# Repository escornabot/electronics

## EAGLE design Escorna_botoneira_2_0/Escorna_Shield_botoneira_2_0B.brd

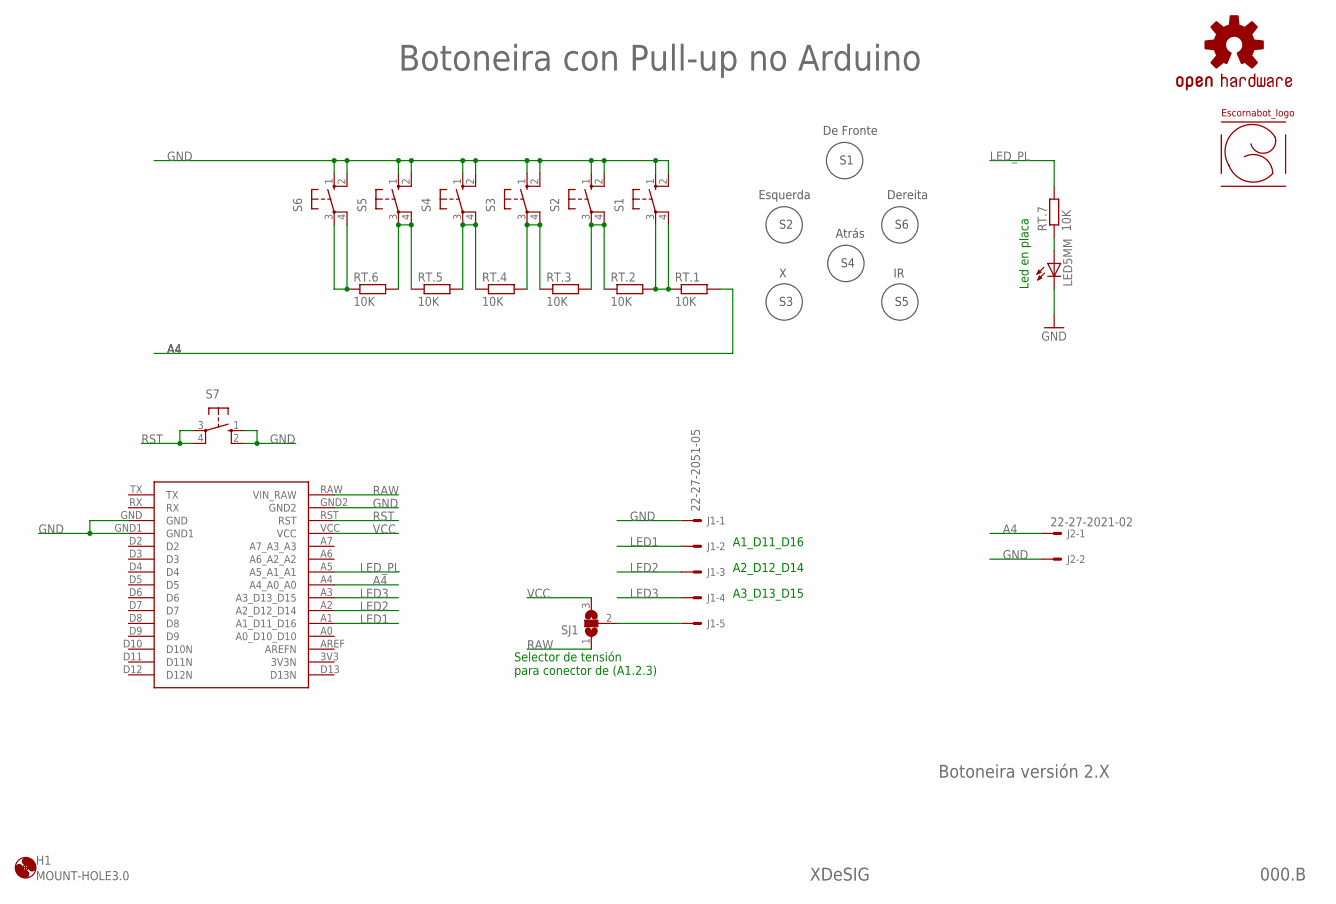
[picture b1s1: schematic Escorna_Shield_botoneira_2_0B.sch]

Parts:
ESSH1: OUTL_ESCORNASHILED; OUTL_ESCORNASHIELD
H1: MOUNT-HOLE3.0; 3,0
J1: 22-27-2051-05; 6410-05
J2: 22-27-2021-02; 6410-02
LED5MM: LED5MM
LOGO2: OSHW-LOGOS; OSHW-LOGO-S
RT.1, RT.2, RT.3, RT.4, RT.5, RT.6, RT.7: 10K; 0204/7
S1, S2, S3, S4, S5, S6: B3F-40XX; B3F40XX_NH
S7: 10-XX; B3F-10XX
SJ1: SOLDERJUMPER_2WAY; SJ_2
U$1: ESCORNABOT; ESCORNA_PEQUE

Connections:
A4: ESSH1.A4 (A4_A0_A0), J2.1, RT.1.2
GND: ESSH1.GND, ESSH1.GND1, ESSH1.GND2, J1.1, J2.2, LED5MM.K (C), S1.1 (S), S1.2 (S1), S2.1 (S), S2.2 (S1), S3.1 (S), S3.2 (S1), S4.1 (S), S4.2 (S1), S5.1 (S), S5.2 (S1), S6.1 (S), S6.2 (S1), S7.1 (S), S7.2 (S1); also elsewhere on the board
LED1: ESSH1.A1 (A1_D11_D16), J1.2
LED2: ESSH1.A2 (A2_D12_D14), J1.3
LED3: ESSH1.A3 (A3_D13_D15), J1.4
LED_PL: ESSH1.A5 (A5_A1_A1), RT.7.2
unnamed 6: LED5MM.A, RT.7.1; also elsewhere on the board
unnamed: J1.5, SJ1.2
unnamed: RT.6.1, S6.3, S6.4 (P1)
unnamed: RT.1.1, RT.2.2, S1.3, S1.4 (P1)
unnamed: RT.2.1, RT.3.2, S2.3, S2.4 (P1)
unnamed: RT.3.1, RT.4.2, S3.3, S3.4 (P1)
unnamed: RT.4.1, RT.5.2, S4.3, S4.4 (P1)
unnamed: RT.5.1, RT.6.2, S5.3, S5.4 (P1)
RAW: ESSH1.RAW (VIN_RAW), SJ1.1
RST: ESSH1.RST, S7.3, S7.4 (P1)
VCC: ESSH1.VCC, SJ1.3

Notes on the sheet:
Botoneira con Pull-up no Arduino
000.B
Botoneira versión 2.X
XDeSIG
De Fronte
Esquerda
Dereita
Atrás
Led en placa
A1_D11_D16
A2_D12_D14
A3_D13_D15
Selector de tensión para conector de (A1.2.3)

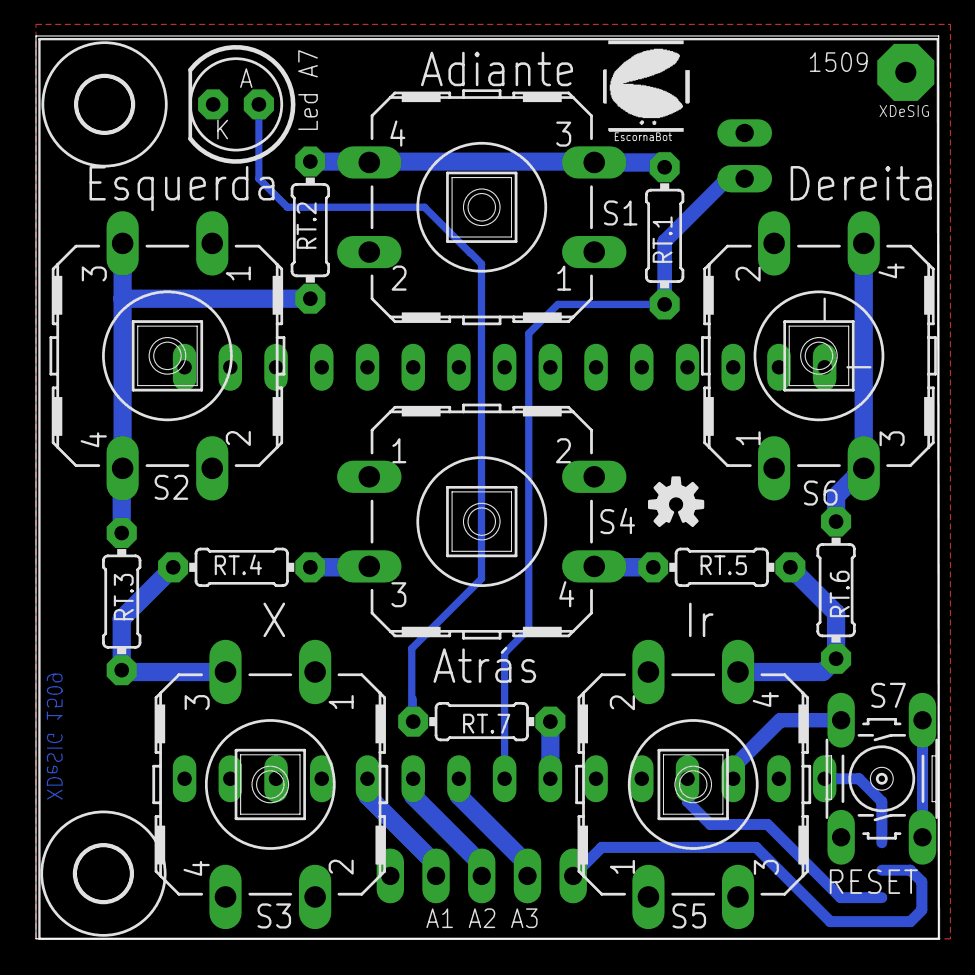
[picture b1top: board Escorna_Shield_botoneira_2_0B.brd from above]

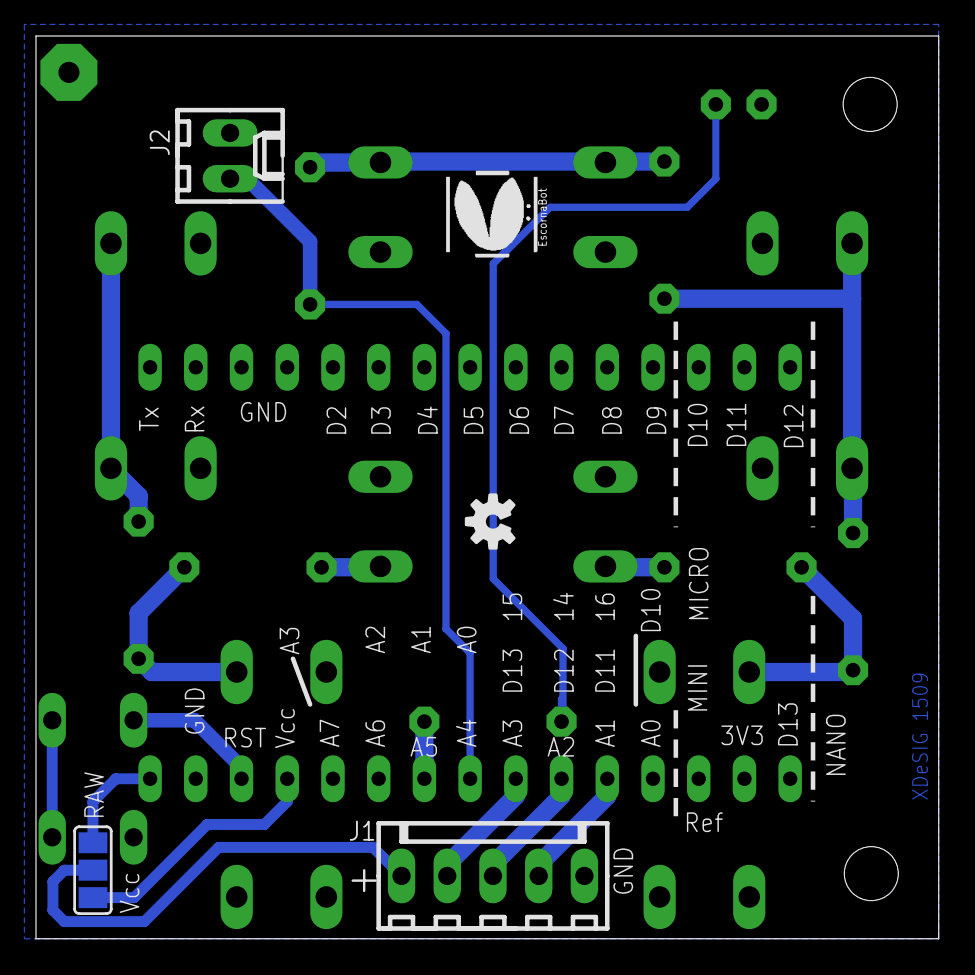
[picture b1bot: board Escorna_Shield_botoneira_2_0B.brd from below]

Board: 2 copper layers, 50.2 x 50.2 mm, 24 parts (5 on the bottom side), 17 nets.

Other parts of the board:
D1: 3 a 5mm; LED5MM
LOGO1: OSHW-LOGOS; OSHW-LOGO-S
U$2: ESCORNABOT; ESCORNA_PEQUE

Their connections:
GND: D1.K; also elsewhere on the board
unnamed 6: D1.A; also elsewhere on the board

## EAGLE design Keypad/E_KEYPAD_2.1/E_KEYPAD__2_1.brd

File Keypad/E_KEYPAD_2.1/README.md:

# Escornabot electronics

## Catalog

- [Escorna CPU][CPU01] (by [Xdesig][XDE01]) is a board to use with
  Arduino Nano. () It integrates keypad on board.
- [Arduino Shield][ARD01] (by [Xdesig][XDE01]) is an Arduino Uno compatible
  shield ready to use with the Escornabot's motors and also integrates a keypad.
- [Cervus][CER01] (by [Xdesig][XDE01]) is a board based on powerful ATmega32u4
  microcontroler and compatible with Arduino shields.
- [Keypad][KEY01] (by [Xdesig][XDE01]) is a 50x50mm board with 5 or 6 buttons and
  connects to any Escornabot.

## License

Every content in this repo, otherwise specified under subdirectories, is
licensed under [Creative Commons BY-SA](LICENSE).

## To buy boards

Developers don't produce boards to sell. Under [_providers_](providers)
directory there are instructions to order yourself.

Are you a board provider? Please, send us your buyer's guide! :)

[CPU01]: EscornaCPU
[ARD01]: ArduinoShield
[CER01]: Cervus
[KEY01]: Keypad
[XDE01]: https://twitter.com/xdesig

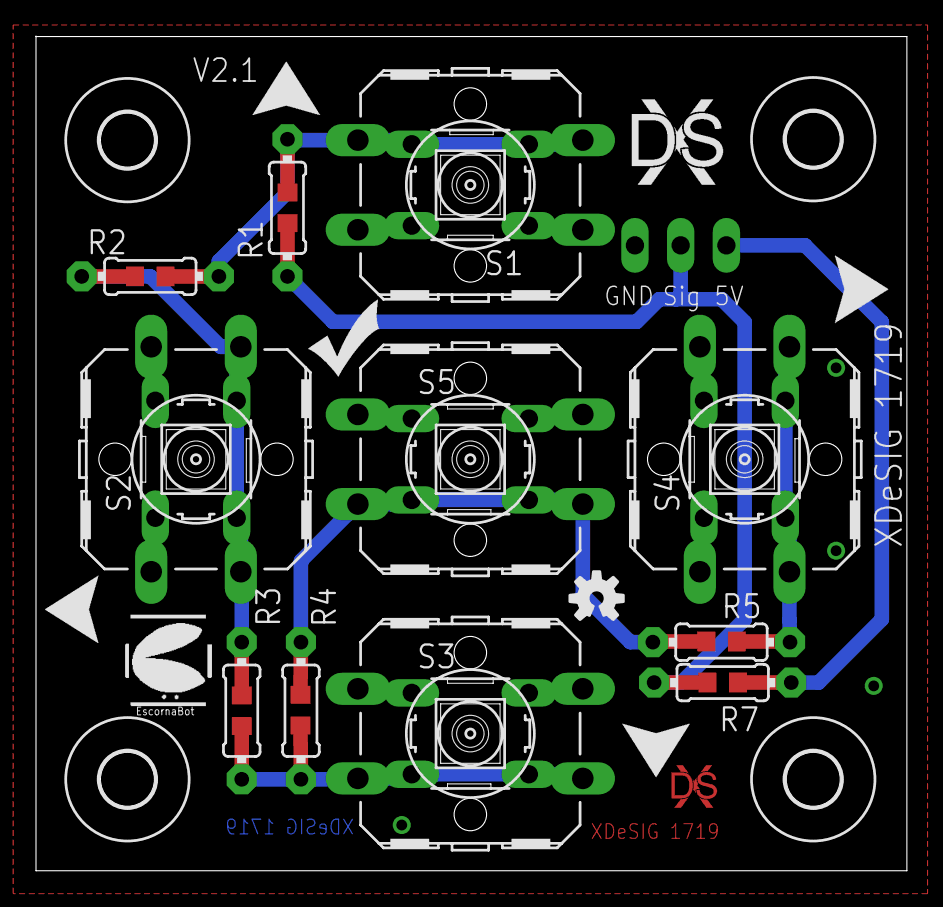
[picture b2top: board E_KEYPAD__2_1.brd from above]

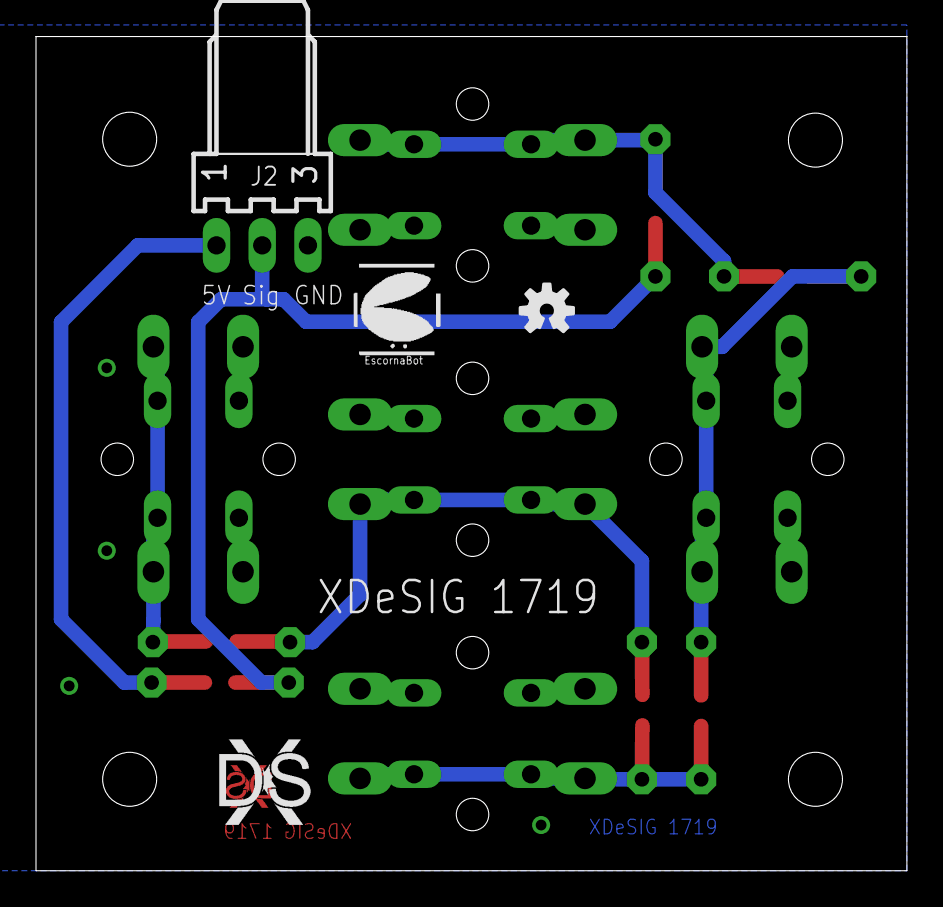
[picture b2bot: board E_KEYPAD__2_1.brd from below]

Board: 2 copper layers, 48.4 x 46.4 mm, 39 parts (4 on the bottom side), 8 nets.

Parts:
H1, H2, H3, H4: HOLE3.0; 3,0
J2: 22-05-7038-03; 7395-03
LOGO1, LOGO2: OSHW-LOGOS; OSHW-LOGO-S
R1, R2, R3, R4, R7: 10K; 0204/7
R1.1, R2.1, R3.1, R4.1, R7.1: 10K; R0603
R5: 22K; 0204/7
R5.1: 22K; R0603
S1, S2, S3, S4, S5: B3F-10XX
S1.1, S2.1, S3.1, S4.1, S5.1: B3F-40XX
U$1, U$2: ESCORNABOT; ESCORNA_PEQUE
U$3, U$4, U$6, U$11: FRECHA
U$5: GO; VALE
U$7, U$9: XDESIG21; XDESIG
U$8: XDESIG; XDESIG_CU_2

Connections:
5V: J2.1, R7.1, R7.1.1
GND: J2.3, S1.1, S1.2, S1.1.1, S1.1.2, S2.1, S2.2, S2.1.1, S2.1.2, S3.1, S3.2, S3.1.1, S3.1.2, S4.1, S4.2, S4.1.1, S4.1.2, S5.1, S5.2, S5.1.1, S5.1.2
S1: R1.1, R1.1.1, R2.2, R2.1.2, S1.3, S1.4, S1.1.3, S1.1.4
S2: R2.1, R2.1.1, R3.2, R3.1.2, S2.3, S2.4, S2.1.3, S2.1.4
S3: R3.1, R3.1.1, R4.2, R4.1.2, S3.3, S3.4, S3.1.3, S3.1.4
S4: R5.1, R5.1.1, S4.3, S4.4, S4.1.3, S4.1.4
S5: R4.1, R4.1.1, R5.2, R5.1.2, S5.3, S5.4, S5.1.3, S5.1.4
SIG: J2.2, R1.2, R1.1.2, R7.2, R7.1.2

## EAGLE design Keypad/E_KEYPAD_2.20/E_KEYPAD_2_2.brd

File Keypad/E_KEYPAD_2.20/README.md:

# E_keyPad 2.20

## Catalog

- [Keypad][KEY01] (by [Xdesig][XDE01]) is a 50x50mm board with 5 buttons, 4 LEDs and
  connects to any Escornabot.

## License

Every content in this repo, otherwise specified under subdirectories, is
licensed under [Creative Commons BY-SA](LICENSE).

## To buy boards

Developers don't produce boards to sell. Under [PCBWAY]

[KEY01]: Keypad
[PCBWAY]: https://www.pcbway.com/project/shareproject/E_KEYPAD_2_2.html
[XDE01]: https://twitter.com/xdesig

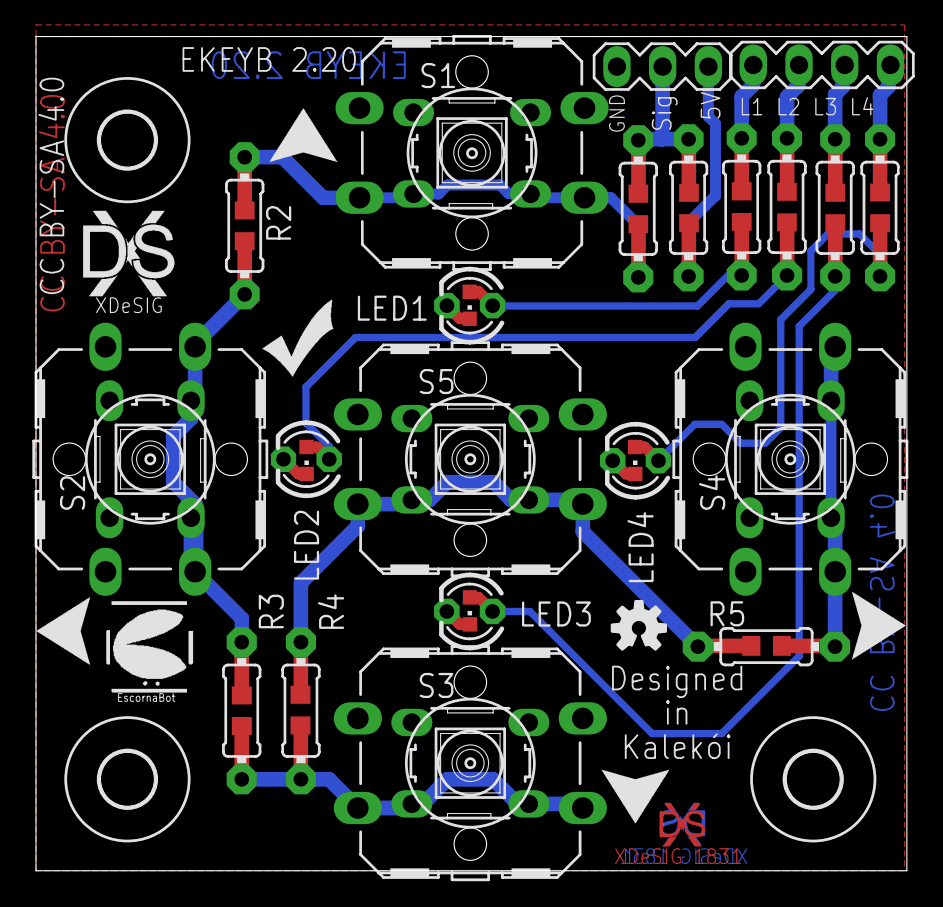
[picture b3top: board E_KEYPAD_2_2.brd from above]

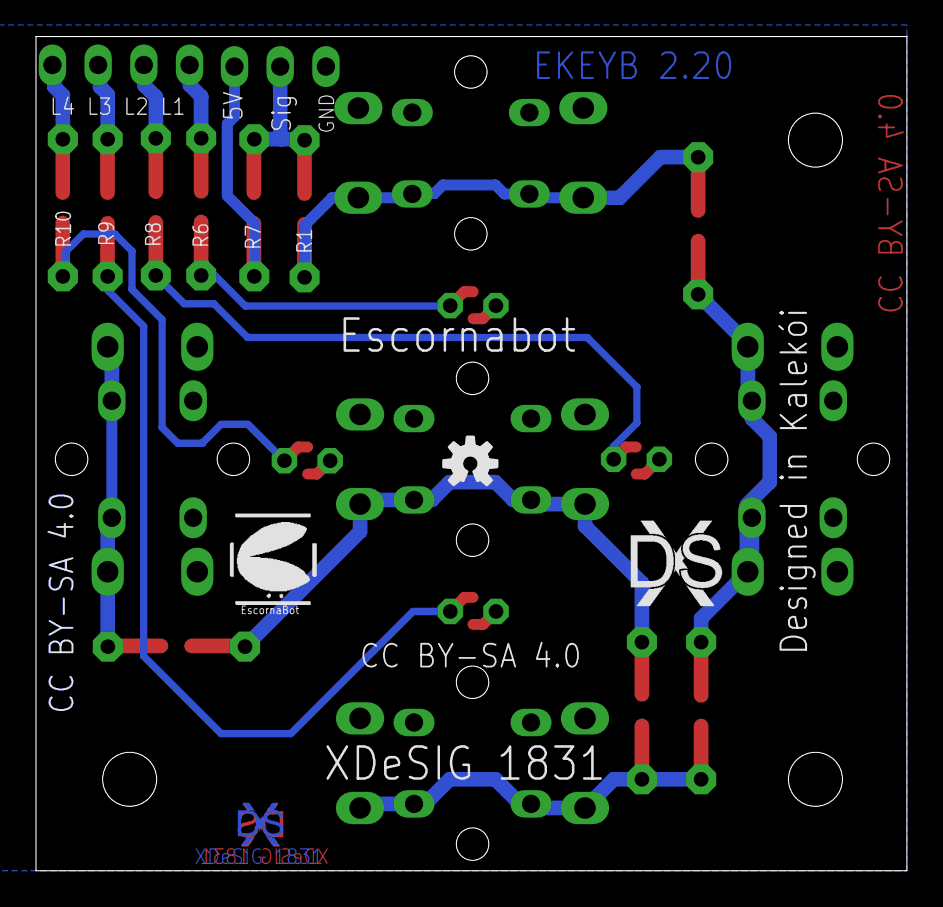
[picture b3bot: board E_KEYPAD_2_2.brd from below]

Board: 2 copper layers, 48.4 x 46.4 mm, 56 parts (4 on the bottom side), 16 nets.

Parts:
H1, H2, H3: HOLE3.0; 3,0
LED1, LED2, LED3, LED4: LED3MM
LED1.1, LED2.1, LED3.1, LED4.1: CHIPLED_0603
LOGO1, LOGO2: OSHW-LOGOS; OSHW-LOGO-S
R1, R2, R3, R4, R7: 10K; 0204/7
R1.1, R2.1, R3.1, R4.1, R7.1: 10K; R0603
R5: 22K; 0204/7
R5.1: 22K; R0603
R6, R8, R9, R10: 1K; 0204/7
R6.1, R8.1, R9.1, R10.1: 1K; R0603
S1, S2, S3, S4, S5: B3F-10XX
S1.1, S2.1, S3.1, S4.1, S5.1: B3F-40XX
SV1: MA04-1
SV2: MA03-1
U$1, U$2: ESCORNABOT; ESCORNA_PEQUE
U$3, U$4, U$6, U$11: FRECHA
U$5: GO; VALE
U$7, U$9: XDESIG21; XDESIG
U$8, U$10: XDESIG; XDESIG_CU_2

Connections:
5V: R7.1, R7.1.1, SV2.1
A0: R6.1, R6.1.1, SV1.1
A1: R8.1, R8.1.1, SV1.2
A2: R9.1, R9.1.1, SV1.3
A3: R10.2, R10.1.1, SV1.4
GND: LED1.K, LED1.1.C, LED2.K, LED2.1.C, LED3.K, LED3.1.C, LED4.K, LED4.1.C, S1.1, S1.2, S1.1.1, S1.1.2, S2.1, S2.2, S2.1.1, S2.1.2, S3.1, S3.2, S3.1.1, S3.1.2, S4.1, S4.2, S4.1.1, S4.1.2, S5.1, S5.2, S5.1.1, S5.1.2, SV2.3
unnamed: LED2.A, LED2.1.A, R8.2, R8.1.2
unnamed: LED1.A, LED1.1.A, R6.2, R6.1.2
unnamed: LED3.A, LED3.1.A, R9.2, R9.1.2
unnamed: LED4.A, LED4.1.A, R10.1, R10.1.2
S1: R1.1, R1.1.1, R2.2, R2.1.2, S1.3, S1.4, S1.1.3, S1.1.4
S2: R2.1, R2.1.1, R3.2, R3.1.2, S2.3, S2.4, S2.1.3, S2.1.4
S3: R3.1, R3.1.1, R4.2, R4.1.2, S3.3, S3.4, S3.1.3, S3.1.4
S4: R5.1, R5.1.1, S4.3, S4.4, S4.1.3, S4.1.4
S5: R4.1, R4.1.1, R5.2, R5.1.2, S5.3, S5.4, S5.1.3, S5.1.4
SIG: R1.2, R1.1.2, R7.2, R7.1.2, SV2.2

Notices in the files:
Escorna_botoneira_2_0/Escorna_Shield_botoneira_2_0B.brd:
Creative Commons Recoñecemento 4.0 Internacional (CC BY 4.0)
Keypad/E_KEYPAD_2.1/E_KEYPAD__2_1.brd:
Creative commons. Attribution-ShareAlike 4.0
International (CC BY-SA 4.0)
Keypad/E_KEYPAD_2.20/E_KEYPAD_2_2.brd:
CC BY-SA 4.0
parts and their libraries:
SparkFun-Aesthetics: Licensing: CC v3.0 Share-Alike You are welcome to use this library for commercial purposes.
